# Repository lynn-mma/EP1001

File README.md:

# EP1001
This is my website to document my journey through Further Digital Fabrication and Prototyping (EP1001) in Singapore Polytechnic. Ihope you enjoy your stay.

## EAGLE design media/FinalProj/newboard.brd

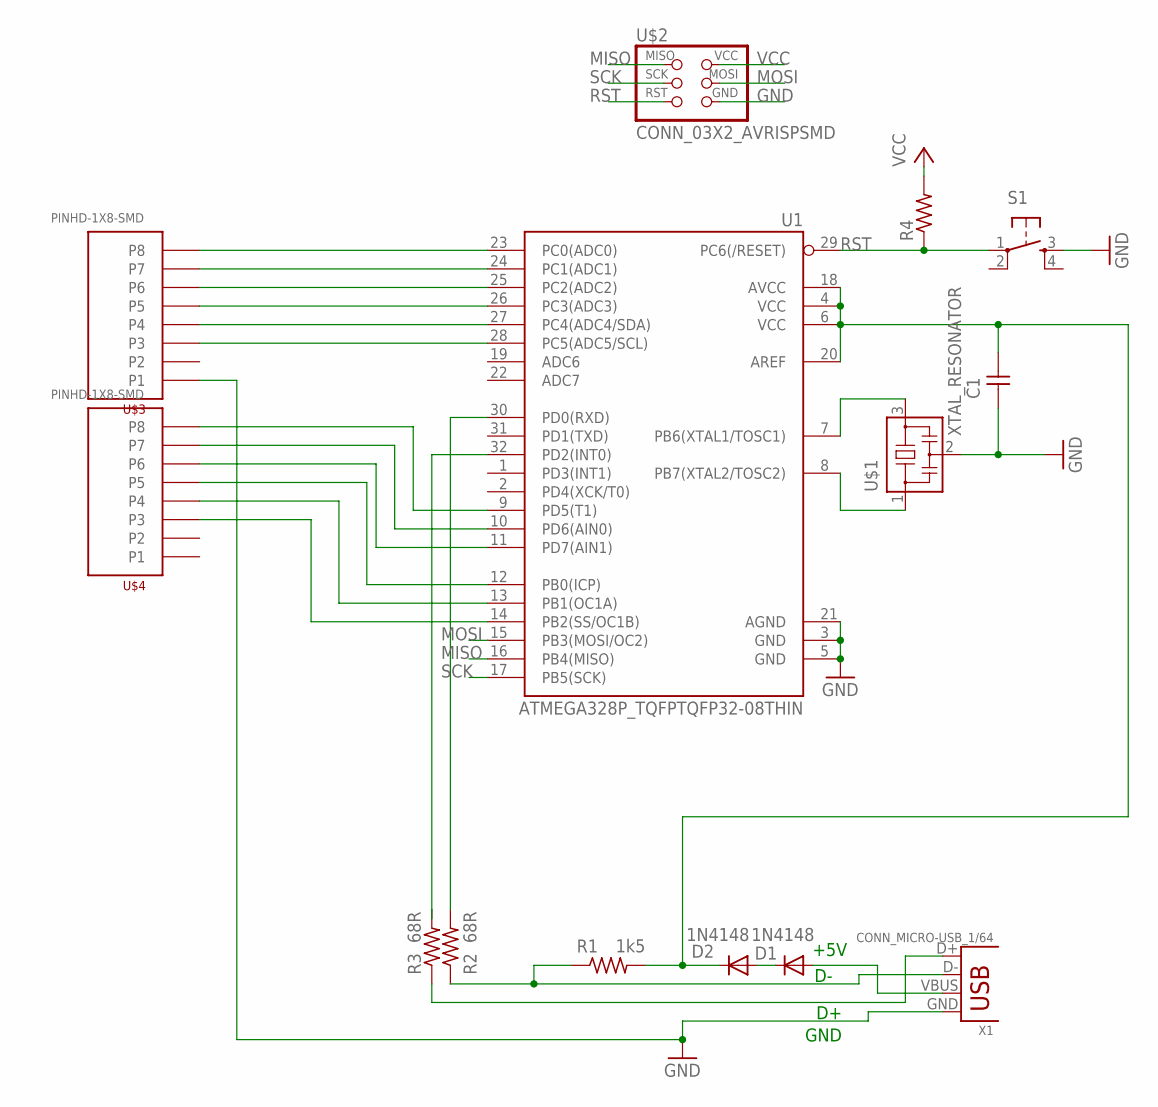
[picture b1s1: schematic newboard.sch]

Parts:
C1: CAP_UNPOLARIZEDFAB; C1206FAB
D1, D2: 1N4148; DO35-10
R1: 1k5; R1206FAB
R2, R3: 68R; R1206FAB
R4: R1206FAB
S1: SW_SWITCH_TACTILE_6MM6MM_SWITCH; 6MM_SWITCH
U1: ATMEGA328P_TQFPTQFP32-08THIN; TQFP32-08THIN
U$1: XTAL_RESONATOR; EFOBM
U$2: CONN_03X2_AVRISPSMD; 2X03SMD
U$3, U$4: PINHD-1X8-SMD; 1X08SMD
X1: CONN_MICRO-USB_1/64; DX4R005HJ5_64

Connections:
GND: C1.1, S1.3 (S), U1.3 (GND), U1.5 (GND), U1.21 (AGND), U$1.2, U$2.6 (GND), U$3.P1, X1.GND
MISO: U1.16 (PB4(MISO)), U$2.1 (MISO)
MOSI: U1.15 (PB3(MOSI/OC2)), U$2.4 (MOSI)
unnamed: U1.23 (PC0(ADC0)), U$3.P8
unnamed: U1.24 (PC1(ADC1)), U$3.P7
unnamed: U1.7 (PB6(XTAL1/TOSC1)), U$1.3
unnamed: U1.8 (PB7(XTAL2/TOSC2)), U$1.1
unnamed: U1.25 (PC2(ADC2)), U$3.P6
unnamed: U1.26 (PC3(ADC3)), U$3.P5
unnamed: R2.2, U1.30 (PD0(RXD))
unnamed: R3.2, U1.32 (PD2(INT0))
unnamed: U1.27 (PC4(ADC4/SDA)), U$3.P4
unnamed: U1.28 (PC5(ADC5/SCL)), U$3.P3
unnamed: U1.9 (PD5(T1)), U$4.P8
unnamed: U1.10 (PD6(AIN0)), U$4.P7
unnamed: U1.11 (PD7(AIN1)), U$4.P6
unnamed: U1.13 (PB1(OC1A)), U$4.P4
unnamed: U1.14 (PB2(SS/OC1B)), U$4.P3
unnamed: R1.1, R2.1, X1.D-
unnamed: R3.1, X1.D+
unnamed: D1.A, X1.VBUS
unnamed: D1.C, D2.A
unnamed: U1.12 (PB0(ICP)), U$4.P5
RST: R4.1, S1.1, U1.29 (PC6(/RESET)), U$2.5 (RST)
SCK: U1.17 (PB5(SCK)), U$2.3 (SCK)
VCC: C1.2, D2.C, R1.2, R4.2, U1.4 (VCC), U1.6 (VCC), U1.18 (AVCC), U1.20 (AREF), U$2.2 (VCC)

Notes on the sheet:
+5V
GND

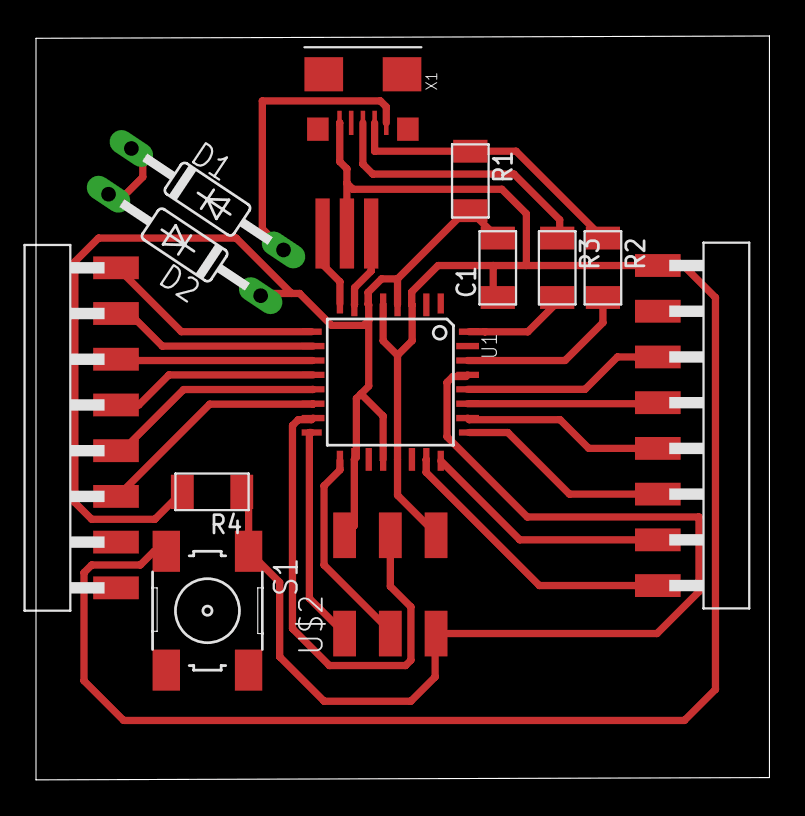
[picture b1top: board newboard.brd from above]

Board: 2 copper layers, 40.7 x 41.3 mm, 14 parts (0 on the bottom side), 26 nets.

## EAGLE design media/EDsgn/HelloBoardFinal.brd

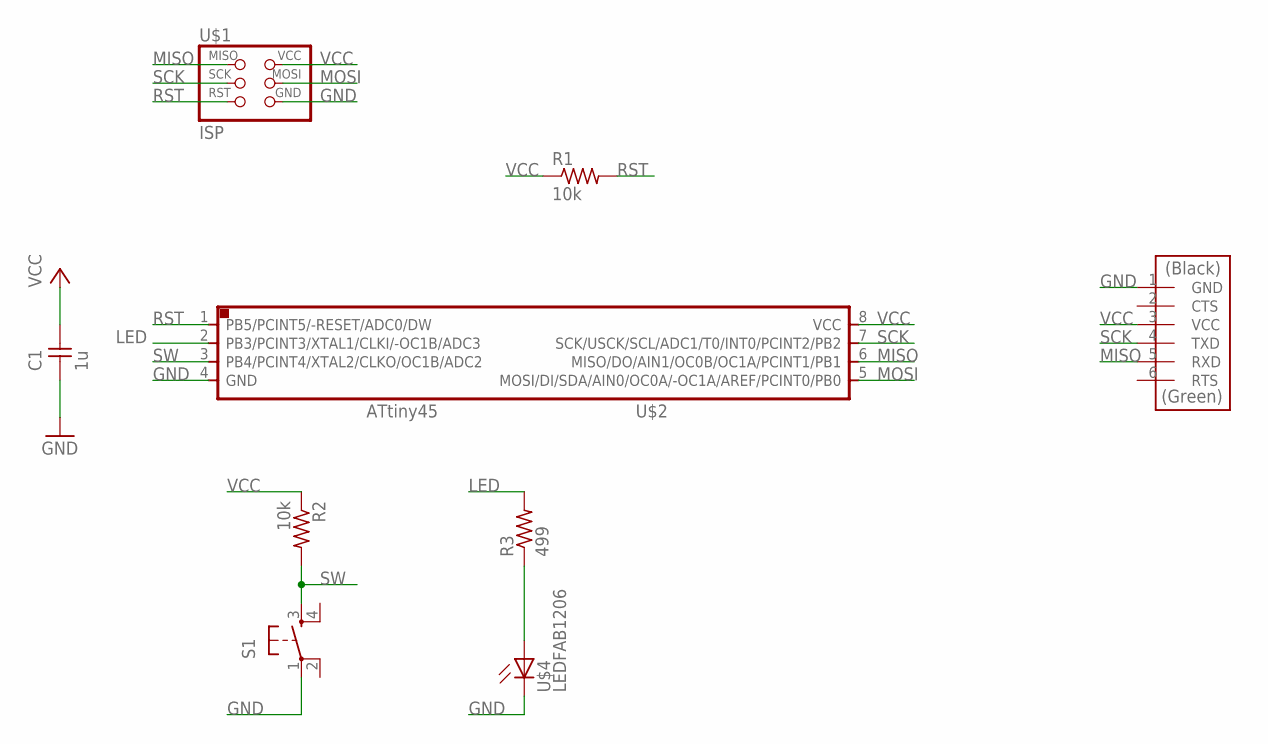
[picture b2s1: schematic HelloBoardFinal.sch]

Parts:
C1: 1u; C1206FAB
R1, R2: 10k; R1206FAB
R3: 499; R1206FAB
S1: SW_SWITCH_TACTILE_6MM6MM_SWITCH; 6MM_SWITCH
U$1: ISP; 2X03SMD
U$2: AT45; SOIC8
U$3: CONN_06_FTDI-SMD-HEADER; 1X06SMD
U$4: LEDFAB1206; LED1206FAB

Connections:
GND: C1.1, S1.1, U$1.6 (GND), U$2.4 (GND), U$3.1 (GND), U$4.2 (C)
LED: R3.2, U$2.2 (PB3/PCINT3/XTAL1/CLKI/-OC1B/ADC3)
MISO: U$1.1 (MISO), U$2.6 (MISO/DO/AIN1/OC0B/OC1A/PCINT1/PB1), U$3.5 (RXD)
MOSI: U$1.4 (MOSI), U$2.5 (MOSI/DI/SDA/AIN0/OC0A/-OC1A/AREF/PCINT0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)
unnamed: R3.1, U$4.1 (A)
RST: R1.2, U$1.5 (RST), U$2.1 (PB5/PCINT5/-RESET/ADC0/DW)
SCK: U$1.3 (SCK), U$2.7 (SCK/USCK/SCL/ADC1/T0/INT0/PCINT2/PB2), U$3.4 (TXD)
SW: R2.2, S1.3 (S), U$2.3 (PB4/PCINT4/XTAL2/CLKO/OC1B/ADC2)
VCC: C1.2, R1.1, R2.1, U$1.2 (VCC), U$2.8 (VCC), U$3.3 (VCC)

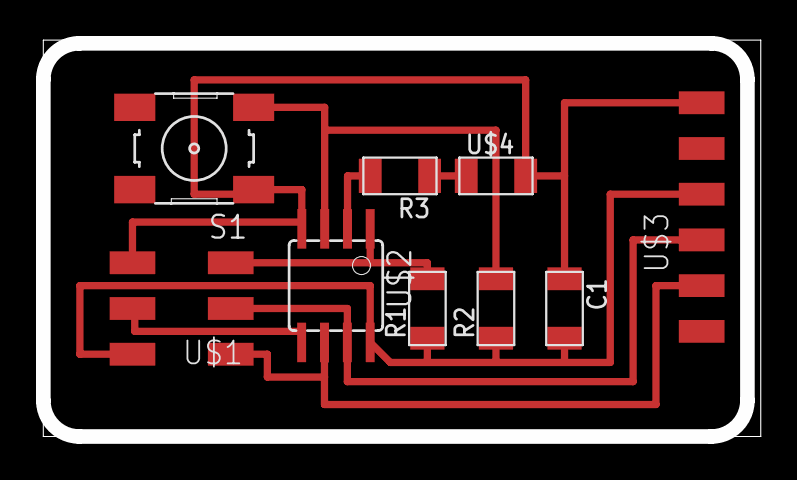
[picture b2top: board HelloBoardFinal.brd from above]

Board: 2 copper layers, 39.5 x 21.8 mm, 9 parts (0 on the bottom side), 9 nets.

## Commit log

2021-11-02 delete
2021-11-02 about
2021-11-02 navbar
2021-11-03 revamp
2021-11-04 test image
2021-11-06 week1
2021-11-06 electronics production
2021-11-06 home image
2021-11-06 schematic
2021-11-22 2->two
2022-01-30 EDesign
2022-01-30 eprod
2022-02-01 2dcnc
2022-02-01 stylesheet change
2022-02-20 many content
2022-02-21 bideo
2022-02-22 picture
2022-02-22 newpic
2022-02-24 embeddProgramming
2022-02-24 content dump
2022-02-24 more content dump
2022-02-24 more changes
2022-02-25 content dump
    changed images to media, content
2022-02-25 minor changes
2022-02-25 minorchanges2
2022-02-26 finalprojdump
2022-02-27 final entry
2022-02-27 actually the last entry
